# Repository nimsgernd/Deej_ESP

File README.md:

# Deej Fork by Daniel Nimsgern

Original deej project (description below) by omriharel

After this project sat idle for so long due to budget reasons I have decided to revive it. The main changes I am looking at are a custom PCB and a switch to using an ESP32 for ease of use and adding wireless capabilities.

The desired feature list is:
- 6 Slide potentiometers
- 6 Mute buttons (Cherry MX Green Switches)
- 2 Rotary potentiometers with switches
- 8 LED mute indicators
- 12 Slide poentiometer indicators
- 4 SPI 128x64 OLED displays

Ideas for a Rev2:
- Li-Ion battery powered (maybe 18650 or pouch cell)

# deej

deej is an **open-source hardware volume mixer** for Windows and Linux PCs. It lets you use real-life sliders (like a DJ!) to **seamlessly control the volumes of different apps** (such as your music player, the game you're playing and your voice chat session) without having to stop what you're doing.

**Join the [deej Discord server](https://discord.gg/nf88NJu) if you need help or have any questions!**

> **_New:_** [work-in-progress deej FAQ](./docs/faq/faq.md)!

deej consists of a [lightweight desktop client](#features) written in Go, and an Arduino-based hardware setup that's simple and cheap to build. [**Check out some versions built by members of our community!**](./community.md)

**[Download the latest release](https://github.com/omriharel/deej/releases/latest) | [Video demonstration](https://youtu.be/VoByJ4USMr8) | [Build video by Tech Always](https://youtu.be/x2yXbFiiAeI)**

> _**Psst!** [No 3D printer? No problem!](./assets/build-shoebox.jpg)_ You can build deej on some cardboard, a shoebox or even a breadboard :)

## Table of contents

- [Deej Fork by Daniel Nimsgern](#deej-fork-by-daniel-nimsgern)
- [deej](#deej)
  - [Table of contents](#table-of-contents)
  - [Features](#features)
  - [How it works](#how-it-works)
    - [Hardware](#hardware)
      - [Schematic](#schematic)
    - [Software](#software)
  - [Slider mapping (configuration)](#slider-mapping-configuration)
  - [Build your own!](#build-your-own)
    - [FAQ](#faq)
    - [Build video](#build-video)
    - [Bill of Materials](#bill-of-materials)
    - [Thingiverse collection](#thingiverse-collection)
    - [Build procedure](#build-procedure)
  - [How to run](#how-to-run)
    - [Requirements](#requirements)
      - [Windows](#windows)
      - [Linux](#linux)
    - [Download and installation](#download-and-installation)
    - [Building from source](#building-from-source)
  - [Community](#community)
    - [Donations](#donations)
    - [Contributing](#contributing)
  - [License](#license)

## Features

deej is written in Go and [distributed](https://github.com/omriharel/deej/releases/latest) as a portable (no installer needed) executable.

- Bind apps to different sliders
  - Bind multiple apps per slider (i.e. one slider for all your games)
  - Bind the master channel
  - Bind "system sounds" (on Windows)
  - Bind specific audio devices by name (on Windows)
  - Bind currently active app (on Windows)
  - Bind all other unassigned apps
- Control your microphone's input level
- Lightweight desktop client, consuming around 10MB of memory
- Runs from your system tray
- Helpful notifications to let you know if something isn't working

> **Looking for the older Python version?** It's no longer maintained, but you can always find it in the [`legacy-python` branch](https://github.com/omriharel/deej/tree/legacy-python).

## How it works

### Hardware

- The sliders are connected to 5 (or as many as you like) analog pins on an Arduino Nano/Uno board. They're powered from the board's 5V output (see schematic)
- The board connects via a USB cable to the PC

#### Schematic

### Software

- The code running on the Arduino board is a [C program](./arduino/deej-5-sliders-vanilla/deej-5-sliders-vanilla.ino) constantly writing current slider values over its serial interface
- The PC runs a lightweight [Go client](./pkg/deej/cmd/main.go) in the background. This client reads the serial stream and adjusts app volumes according to the given configuration file

## Slider mapping (configuration)

deej uses a simple YAML-formatted configuration file named [`config.yaml`](./config.yaml), placed alongside the deej executable.

The config file determines which applications (and devices) are mapped to which sliders, and which parameters to use for the connection to the Arduino board, as well as other user preferences.

**This file auto-reloads when its contents are changed, so you can change application mappings on-the-fly without restarting deej.**

It looks like this:

```yaml
slider_mapping:
  0: master
  1: chrome.exe
  2: spotify.exe
  3:
    - pathofexile_x64.exe
    - rocketleague.exe
  4: discord.exe

# set this to true if you want the controls inverted (i.e. top is 0%, bottom is 100%)
invert_sliders: false

# settings for connecting to the arduino board
com_port: COM4
baud_rate: 9600

# adjust the amount of signal noise reduction depending on your hardware quality
# supported values are "low" (excellent hardware), "default" (regular hardware) or "high" (bad, noisy hardware)
noise_reduction: default
```

- `master` is a special option to control the master volume of the system _(uses the default playback device)_
- `mic` is a special option to control your microphone's input level _(uses the default recording device)_
- `deej.unmapped` is a special option to control all apps that aren't bound to any slider ("everything else")
- On Windows, `deej.current` is a special option to control whichever app is currently in focus
- On Windows, you can specify a device's full name, i.e. `Speakers (Realtek High Definition Audio)`, to bind that device's level to a slider. This doesn't conflict with the default `master` and `mic` options, and works for both input and output devices.
  - Be sure to use the full device name, as seen in the menu that comes up when left-clicking the speaker icon in the tray menu
- `system` is a special option on Windows to control the "System sounds" volume in the Windows mixer
- All names are case-**in**sensitive, meaning both `chrome.exe` and `CHROME.exe` will work
- You can create groups of process names (using a list) to either:
    - control more than one app with a single slider
    - choose whichever process in the group that's currently running (i.e. to have one slider control any game you're playing)

## Build your own!

Building deej is very simple. You only need a few relatively cheap parts - it's an excellent starter project (and my first Arduino project, personally). Remember that if you need any help or have a question that's not answered here, you can always [join the deej Discord server](https://discord.gg/nf88NJu).

Build deej for yourself, or as an awesome gift for your gaming buddies!

### FAQ

I've started a highly focused effort of writing a proper FAQ page for deej, covering many basic and advanced topics.

It is still _very much a work-in-progress_, but I'm happy to [share it in its current state](./docs/faq/faq.md) in hopes that it at least covers some questions you might have.

FAQ feedback in our [community Discord](https://discord.gg/nf88NJu) is strongly encouraged :)

### Build video

In case you prefer watching to reading, Charles from the [**Tech Always**](https://www.youtube.com/c/TechAlways) YouTube channel has made [**a fantastic video**](https://youtu.be/x2yXbFiiAeI) that covers the basics of building deej for yourself, including parts, costs, assembly and software. I highly recommend checking it out!

### Bill of Materials

- An Arduino Nano, Pro Micro or Uno board
  - I officially recommend using a Nano or a Pro Micro for their smaller form-factor, friendlier USB connectors and more analog pins. Plus they're cheaper
  - You can also use any other development board that has a Serial over USB interface
- A few slider potentiometers, up to your number of free analog pins (the cheaper ones cost around 1-2 USD each, and come with a standard 10K Ohm variable resistor. These _should_ work just fine for this project)
  - **Important:** make sure to get **linear** sliders, not logarithmic ones! Check the product description
  - You can also use circular knobs if you like
- Some wires
- Any kind of box to hold everything together. **You don't need a 3D printer for this project!** It works fantastically with just a piece of cardboard or a shoebox. That being said, if you do have one, read on...

### Thingiverse collection

With many different 3D-printed designs being added to our [community showcase](./community.md), it felt right to gather all of them in a Thingiverse collection for you to browse. If you have access to a 3D printer, feel free to use one of the designs in your build.

**[Visit our community-created design collection on Thingiverse!](https://thingiverse.com/omriharel/collections/deej)**

> You can also [submit your own](https://discord.gg/nf88NJu) design to be added to the collection. Regardless, if you do upload your design to Thingiverse, _please add a `deej` tag to it so that others can find it more easily_.

### Build procedure

- Connect everything according to the [schematic](#schematic)
- Test with a multimeter to be sure your sliders are hooked up correctly
- Flash the Arduino chip with the sketch in [`arduino\deej-5-sliders-vanilla`](./arduino/deej-5-sliders-vanilla/deej-5-sliders-vanilla.ino)
  - _Important:_ If you have more or less than 5 sliders, you must edit the sketch to match what you have
- After flashing, check the serial monitor. You should see a constant stream of values separated by a pipe (`|`) character, e.g. `0|240|1023|0|483`
  - When you move a slider, its corresponding value should move between 0 and 1023
- Congratulations, you're now ready to run the deej executable!

## How to run

### Requirements

#### Windows

- Windows. That's it

#### Linux

- Install `libgtk-3-dev`, `libappindicator3-dev` and `libwebkit2gtk-4.0-dev` for system tray support. Pre-built Linux binaries aren't currently released, so you'll need to [build from source](#building-from-source). If there's demand for pre-built binaries, please [let me know](https://discord.gg/nf88NJu)!

### Download and installation

- Head over to the [releases page](https://github.com/omriharel/deej/releases) and download the [latest version](https://github.com/omriharel/deej/releases/latest)'s executable and configuration file (`deej.exe` and `config.yaml`)
- Place them in the same directory anywhere on your machine
- (Optional, on Windows) Create a shortcut to `deej.exe` and copy it to `%APPDATA%\Microsoft\Windows\Start Menu\Programs\Startup` to have deej run on boot

### Building from source

If you'd rather not download a compiled executable, or want to extend deej or modify it to your needs, feel free to clone the repository and build it yourself. All you need is a Go 1.14 (or above) environment on your machine. If you go this route, make sure to check out the [developer scripts](./pkg/deej/scripts).

Like other Go packages, you can also use the `go get` tool: `go get -u github.com/omriharel/deej`. Please note that the package code now resides in the `pkg/deej` directory, and needs to be imported from there if used inside another project.

If you need any help with this, please [join our Discord server](https://discord.gg/nf88NJu).

## Community

deej is a relatively new project, but a vibrant and awesome community is rapidly growing around it. Come hang out with us in the [deej Discord server](https://discord.gg/nf88NJu), or check out a whole bunch of cool and creative builds made by our members in the [community showcase](./community.md).

The server is also a great place to ask questions, suggest features or report bugs (but of course, feel free to use GitHub if you prefer).

### Donations

If you love deej and want to show your support for this project, you can do so using the link below. Please don't feel obligated to donate - building the project and telling your friends about it goes a very long way! Thank you very much.

### Contributing

Please see [`docs/CONTRIBUTING.md`](./docs/CONTRIBUTING.md).

## License

deej is released under the [MIT license](./LICENSE).

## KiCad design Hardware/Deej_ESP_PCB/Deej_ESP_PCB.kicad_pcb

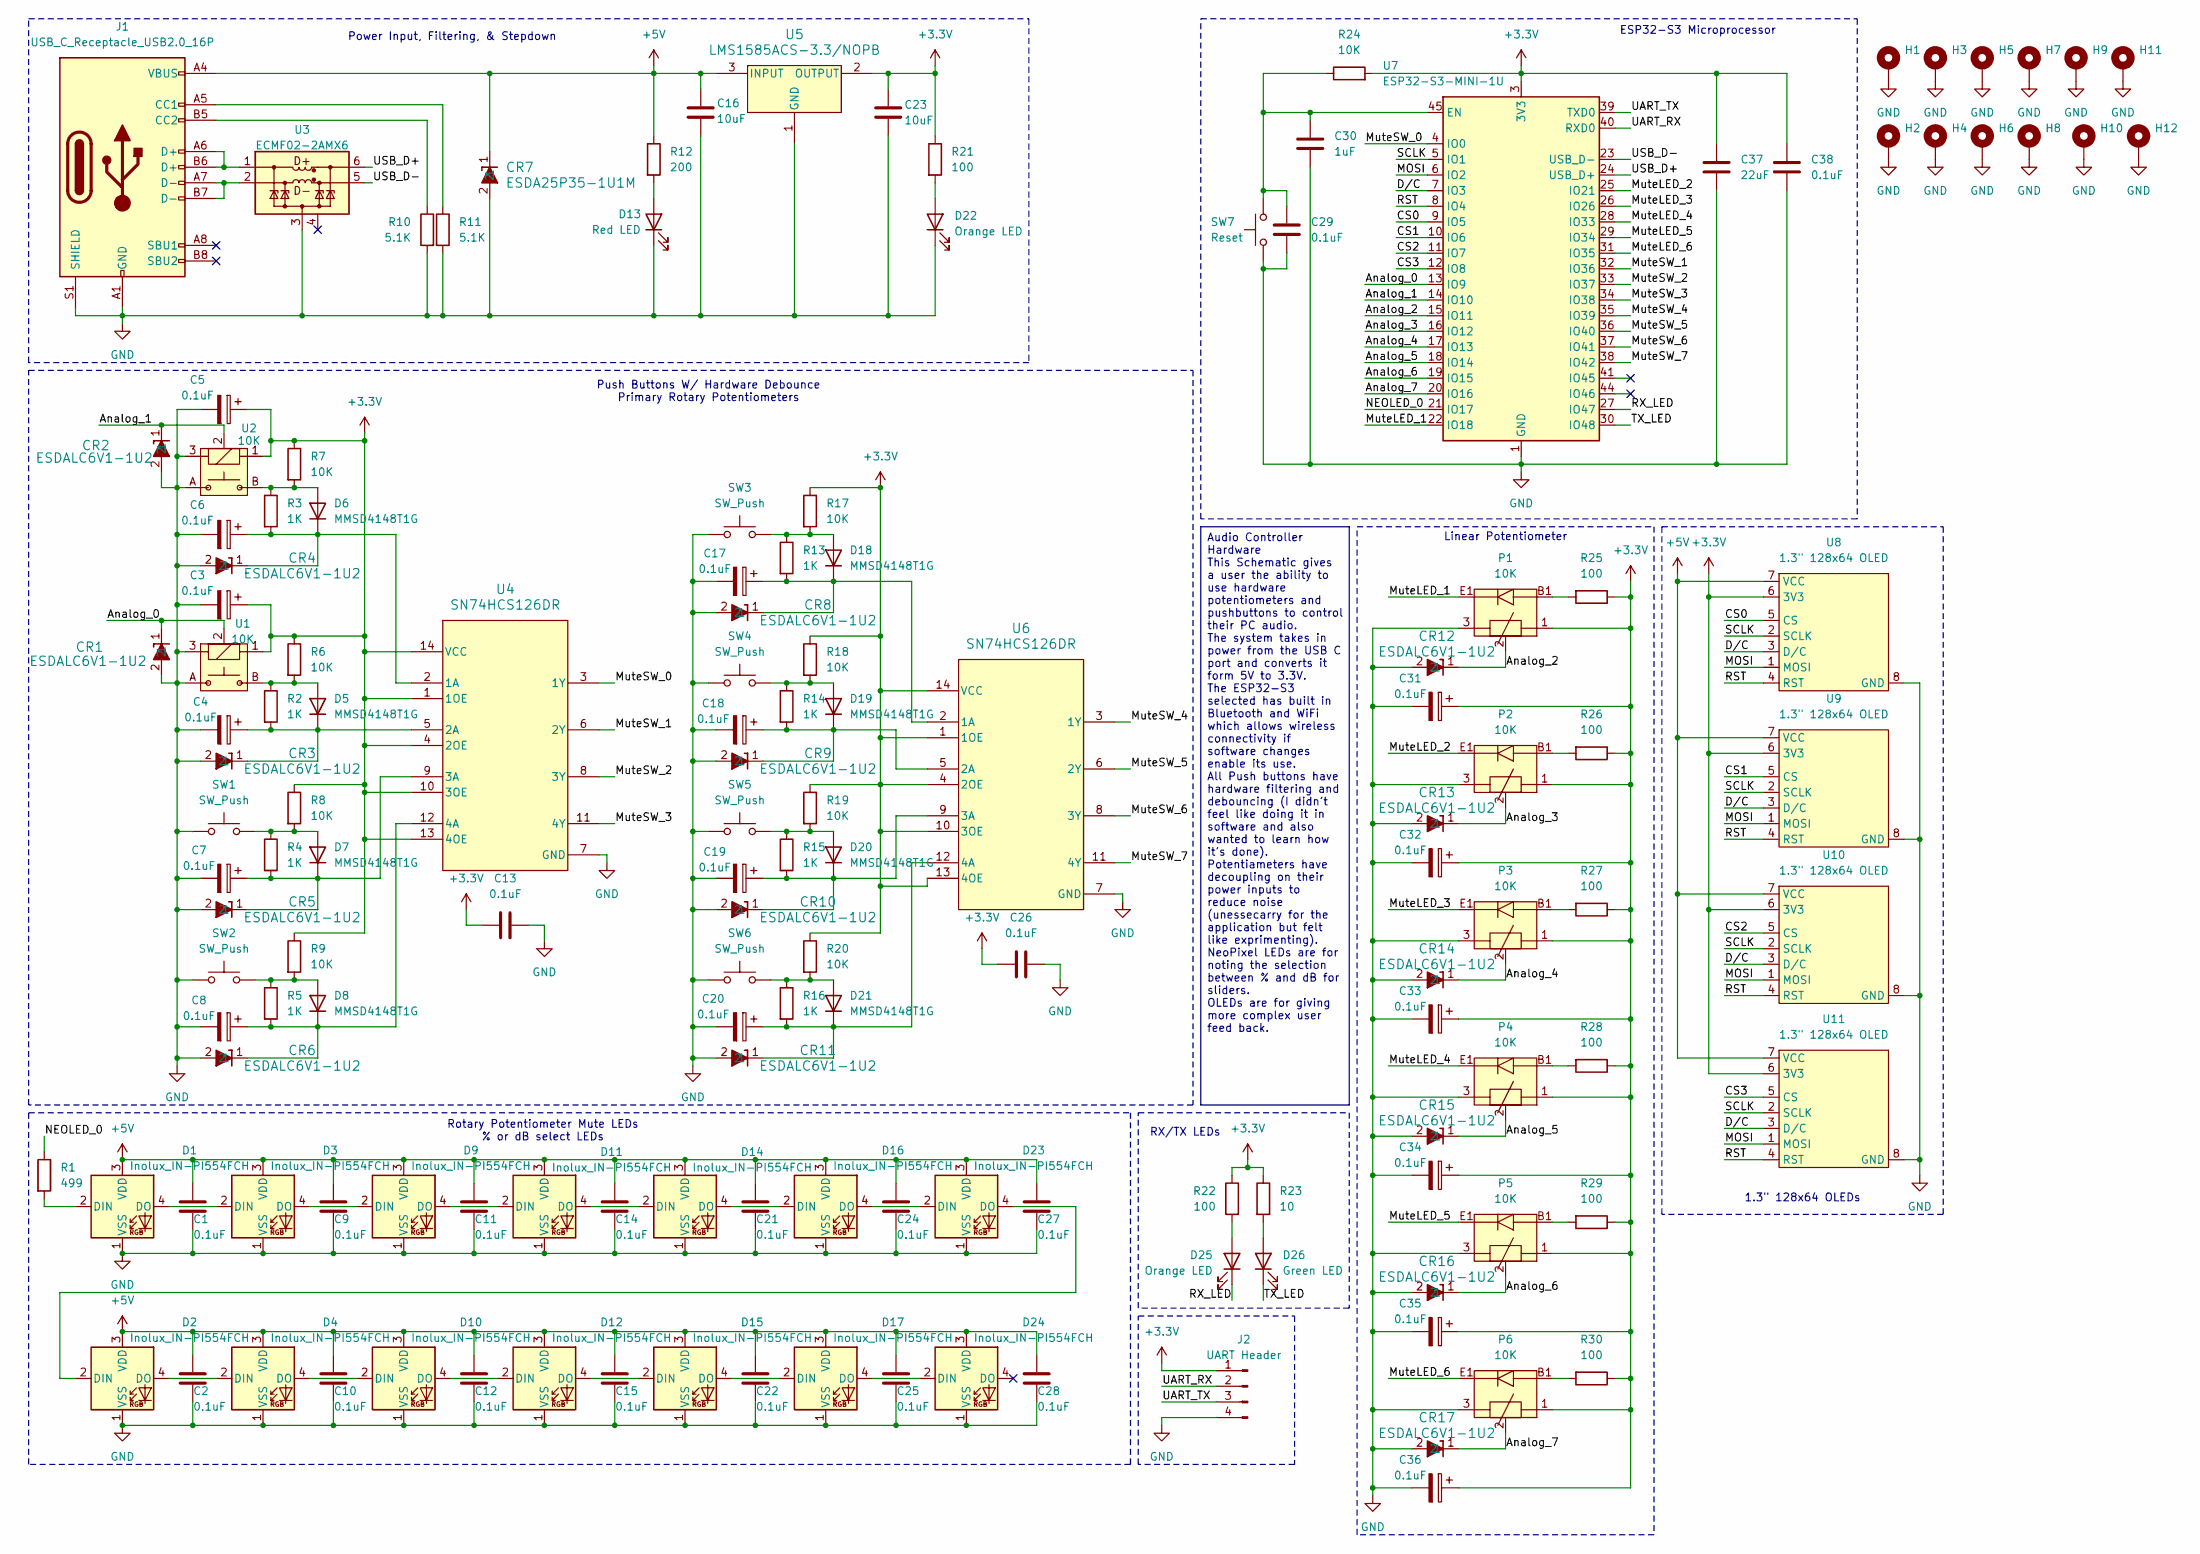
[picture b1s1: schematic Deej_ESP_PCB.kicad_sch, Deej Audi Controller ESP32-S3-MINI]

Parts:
C1, C2, C9, C10, C11, C12, C13, C14, C15, C21, C22, C24, C25, C26, C27, C28, C29, C38: 0.1uF; C_0603_1608Metric_Pad1.08x0.95mm_HandSolder
C3, C4, C5, C6, C7, C8, C17, C18, C19, C20, C31, C32, C33, C34, C35, C36: 0.1uF; CP_EIA-3216-18_Kemet-A_HandSolder
C16, C23: 10uF; C_0603_1608Metric_Pad1.08x0.95mm_HandSolder
C30: 1uF; C_0603_1608Metric_Pad1.08x0.95mm_HandSolder
C37: 22uF; C_0603_1608Metric_Pad1.08x0.95mm_HandSolder
CR1, CR2, CR3, CR4, CR5, CR6, CR8, CR9, CR10, CR11, CR12, CR13, CR14, CR15, CR16, CR17: ESDALC6V1-1U2; DIODE_ESDALC6V1-1U2_STM
CR7: ESDA25P35-1U1M; QFN1610_STM
D1, D2, D3, D4, D9, D10, D11, D12, D14, D15, D16, D17, D23, D24: Inolux_IN-PI554FCH; LED_Inolux_IN-PI554FCH_PLCC4_5.0x5.0mm_P3.2mm
D5, D6, D7, D8, D18, D19, D20, D21: MMSD4148T1G; D_SOD-123
D13: Red LED; LED_0603_1608Metric_Pad1.05x0.95mm_HandSolder
D22, D25: Orange LED; LED_0603_1608Metric_Pad1.05x0.95mm_HandSolder
D26: Green LED; LED_0603_1608Metric_Pad1.05x0.95mm_HandSolder
H1, H3, H5, H7, H9: MountingHole_3.2mm_M3_Pad
H2, H4, H6, H8, H10, H11, H12: MountingHole_Pad; MountingHole_3.2mm_M3_Pad
J1: USB_C_Receptacle_USB2.0_16P; USB_C_Receptacle_GCT_USB4085
J2: UART Header; PinHeader_1x04_P2.54mm_Vertical
P1, P2, P3, P4, P5, P6: 10K; PTL0115R0103B1
R1: 499; C_0603_1608Metric_Pad1.08x0.95mm_HandSolder
R2, R3, R4, R5, R13, R14, R15, R16: 1K; C_0603_1608Metric_Pad1.08x0.95mm_HandSolder
R6, R7, R8, R9, R17, R18, R19, R20, R24: 10K; C_0603_1608Metric_Pad1.08x0.95mm_HandSolder
R10, R11: 5.1K; C_0603_1608Metric_Pad1.08x0.95mm_HandSolder
R12: 200; C_0603_1608Metric_Pad1.08x0.95mm_HandSolder
R21, R22, R25, R26, R27, R28, R29, R30: 100; C_0603_1608Metric_Pad1.08x0.95mm_HandSolder
R23: 10; C_0603_1608Metric_Pad1.08x0.95mm_HandSolder
SW1, SW2, SW3, SW4, SW5, SW6: SW_Push; SW_Cherry_MX_PCB
SW7: Reset; SWITCH_FSMSM_TYC
U1, U2: 10K; 39LA-1PB-103
U3: ECMF02-2AMX6; QFN-6L_STM
U4, U6: SN74HCS126DR; D0014A-IPC_A
U5: LMS1585ACS-3.3/NOPB; KTT0003B
U7: ESP32-S3-MINI-1U; ESP32S3MINI1UN8
U8, U9, U10, U11: 1.3" 128x64 OLED; Adafruit_1_3_OLED

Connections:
+3.3V: C3.1, C5.1, C13.2, C23.1, C26.2, C31.1, C32.1, C33.1, C34.1, C35.1, C36.1, C37.1, C38.1, J2.1, P1.1, P2.1, P3.1, P4.1, P5.1, P6.1, R6.1, R7.1, R8.1, R9.1, R17.1, R18.1, R19.1, R20.1, R21.1, R22.1, R23.1, R24.2, R25.1, R26.1, R27.1, R28.1, R29.1, R30.1, U1.1, U2.1, U4.1 (1OE), U4.4 (2OE), U4.10 (3OE), U4.13 (4OE), U4.14 (VCC), U5.2 (OUTPUT), U5.4 (OUTPUT), U6.1 (1OE), U6.4 (2OE), U6.10 (3OE), U6.13 (4OE), U6.14 (VCC), U7.3 (3V3), U8.6 (3V3), U9.6 (3V3), U10.6 (3V3), U11.6 (3V3)
+5V: C1.1, C2.1, C9.1, C10.1, C11.1, C12.1, C14.1, C15.1, C16.1, C21.1, C22.1, C24.1, C25.1, C27.1, C28.1, CR7.1, D1.3 (VDD), D2.3 (VDD), D3.3 (VDD), D4.3 (VDD), D9.3 (VDD), D10.3 (VDD), D11.3 (VDD), D12.3 (VDD), D14.3 (VDD), D15.3 (VDD), D16.3 (VDD), D17.3 (VDD), D23.3 (VDD), D24.3 (VDD), J1.A4 (VBUS), J1.A9 (VBUS), J1.B4 (VBUS), J1.B9 (VBUS), R12.1, U5.3 (INPUT), U8.7 (VCC), U9.7 (VCC), U10.7 (VCC), U11.7 (VCC)
/Analog_0: CR1.1, U1.2, U7.13 (IO9)
/Analog_1: CR2.1, U2.2, U7.14 (IO10)
/Analog_2: CR12.1, P1.2, U7.15 (IO11)
/Analog_3: CR13.1, P2.2, U7.16 (IO12)
/Analog_4: CR14.1, P3.2, U7.17 (IO13)
/Analog_5: CR15.1, P4.2, U7.18 (IO14)
/Analog_6: CR16.1, P5.2, U7.19 (IO15)
/Analog_7: CR17.1, P6.2, U7.20 (IO16)
/CS0: U7.9 (IO5), U8.5 (CS)
/CS1: U7.10 (IO6), U9.5 (CS)
/CS2: U7.11 (IO7), U10.5 (CS)
/CS3: U7.12 (IO8), U11.5 (CS)
/D/C: U7.7 (IO3), U8.3 (D/C), U9.3 (D/C), U10.3 (D/C), U11.3 (D/C)
/MOSI: U7.6 (IO2), U8.1 (MOSI), U9.1 (MOSI), U10.1 (MOSI), U11.1 (MOSI)
/MuteLED_1: P1.E1, U7.22 (IO18)
/MuteLED_2: P2.E1, U7.25 (IO21)
/MuteLED_3: P3.E1, U7.26 (IO26)
/MuteLED_4: P4.E1, U7.28 (IO33)
/MuteLED_5: P5.E1, U7.29 (IO34)
/MuteLED_6: P6.E1, U7.31 (IO35)
/MuteSW_0: U4.3 (1Y), U7.4 (IO0)
/MuteSW_1: U4.6 (2Y), U7.32 (IO36)
/MuteSW_2: U4.8 (3Y), U7.33 (IO37)
/MuteSW_3: U4.11 (4Y), U7.34 (IO38)
/MuteSW_4: U6.3 (1Y), U7.35 (IO39)
/MuteSW_5: U6.6 (2Y), U7.36 (IO40)
/MuteSW_6: U6.8 (3Y), U7.37 (IO41)
/MuteSW_7: U6.11 (4Y), U7.38 (IO42)
/NEOLED_0: R1.1, U7.21 (IO17)
/RST: U7.8 (IO4), U8.4 (RST), U9.4 (RST), U10.4 (RST), U11.4 (RST)
/RX_LED: D25.1 (K), U7.27 (IO47)
/SCLK: U7.5 (IO1), U8.2 (SCLK), U9.2 (SCLK), U10.2 (SCLK), U11.2 (SCLK)
/TX_LED: D26.1 (K), U7.30 (IO48)
/UART_RX: J2.2, U7.40 (RXD0)
/UART_TX: J2.3, U7.39 (TXD0)
/USB_D+: U3.6 (D+_out), U7.24 (USB_D+)
/USB_D-: U3.5 (D-_out), U7.23 (USB_D-)
GND: C1.2, C2.2, C3.2, C4.2, C5.2, C6.2, C7.2, C8.2, C9.2, C10.2, C11.2, C12.2, C13.1, C14.2, C15.2, C16.2, C17.2, C18.2, C19.2, C20.2, C21.2, C22.2, C23.2, C24.2, C25.2, C26.1, C27.2, C28.2, C29.2, C30.2, C31.2, C32.2, C33.2, C34.2, C35.2, C36.2, C37.2, C38.2, CR1.2, CR2.2, CR3.2, CR4.2, CR5.2, CR6.2, CR7.2, CR8.2, CR9.2, CR10.2, CR11.2, CR12.2, CR13.2, CR14.2, CR15.2, CR16.2, CR17.2, D1.1 (VSS), D2.1 (VSS), D3.1 (VSS), D4.1 (VSS), D9.1 (VSS), D10.1 (VSS), D11.1 (VSS), D12.1 (VSS), D13.1 (K), D14.1 (VSS), D15.1 (VSS), D16.1 (VSS), D17.1 (VSS), D22.1 (K), D23.1 (VSS), D24.1 (VSS), H1.1, H2.1, H3.1, H4.1, H5.1, H6.1, H7.1, H8.1, H9.1, H10.1, H11.1, H12.1, J1.A1 (GND), J1.A12 (GND), J1.B1 (GND), J1.B12 (GND), J1.S1 (SHIELD), J2.4, P1.3, P2.3, P3.3, P4.3, P5.3, P6.3, R10.2, R11.2, SW1.1, SW2.1, SW3.1, SW4.1, SW5.1, SW6.1, SW7.1, U1.3, U1.A, U2.3, U2.A, U3.3 (GND), U4.7 (GND), U5.1 (GND), U6.7 (GND), U7.1 (GND), U7.2 (GND), U7.42 (GND), U7.43 (GND), U7.46 (GND), U7.47 (GND), U7.48 (GND), U7.49 (GND), U7.50 (GND), U7.51 (GND), U7.52 (GND), U7.53 (GND), U7.54 (GND), U7.55 (GND), U7.56 (GND), U7.57 (GND), U7.58 (GND), U7.59 (GND), U7.60 (GND), U7.61 (GND), U7.62 (GND), U7.63 (GND), U7.64 (GND), U7.65 (GND), U7.66 (GND), U7.67 (GND), U7.68 (GND), U7.69 (GND), U7.70 (GND), U7.71 (GND), U7.72 (GND), U7.73 (GND), U8.8 (GND), U9.8 (GND), U10.8 (GND), U11.8 (GND)
unnamed: D1.2 (DIN), R1.2
unnamed: D1.4 (DO), D3.2 (DIN)
unnamed: D2.2 (DIN), D23.4 (DO)
unnamed: D2.4 (DO), D4.2 (DIN)
unnamed: D3.4 (DO), D9.2 (DIN)
unnamed: D5.2 (A), R2.1, R6.2, U1.B
unnamed: C4.1, CR3.1, D5.1 (K), R2.2, U4.5 (2A)
unnamed: D6.2 (A), R3.1, R7.2, U2.B
unnamed: C6.1, CR4.1, D6.1 (K), R3.2, U4.2 (1A)
unnamed: D7.2 (A), R4.1, R8.2, SW1.2
unnamed: C7.1, CR5.1, D7.1 (K), R4.2, U4.9 (3A)
unnamed: D8.2 (A), R5.1, R9.2, SW2.2
unnamed: C8.1, CR6.1, D8.1 (K), R5.2, U4.12 (4A)
unnamed: D4.4 (DO), D10.2 (DIN)
unnamed: D10.4 (DO), D12.2 (DIN)
unnamed: D9.4 (DO), D11.2 (DIN)
unnamed: D11.4 (DO), D14.2 (DIN)
unnamed: D12.4 (DO), D15.2 (DIN)
unnamed: D13.2 (A), R12.2
unnamed: D14.4 (DO), D16.2 (DIN)
unnamed: D15.4 (DO), D17.2 (DIN)
unnamed: D16.4 (DO), D23.2 (DIN)
unnamed: D17.4 (DO), D24.2 (DIN)
unnamed: D18.2 (A), R13.1, R17.2, SW3.2
unnamed: C17.1, CR8.1, D18.1 (K), R13.2, U6.2 (1A)
unnamed: D19.2 (A), R14.1, R18.2, SW4.2
unnamed: C18.1, CR9.1, D19.1 (K), R14.2, U6.5 (2A)
unnamed: D20.2 (A), R15.1, R19.2, SW5.2
unnamed: C19.1, CR10.1, D20.1 (K), R15.2, U6.9 (3A)
unnamed: D21.2 (A), R16.1, R20.2, SW6.2
unnamed: C20.1, CR11.1, D21.1 (K), R16.2, U6.12 (4A)
unnamed: D22.2 (A), R21.2
unnamed: D25.2 (A), R22.2
unnamed: D26.2 (A), R23.2
unnamed: J1.A5 (CC1), R11.1
unnamed: J1.B5 (CC2), R10.1
unnamed: P1.B1, R25.2
unnamed: P2.B1, R26.2
unnamed: P3.B1, R27.2
unnamed: P4.B1, R28.2
unnamed: P5.B1, R29.2
unnamed: P6.B1, R30.2
unnamed: J1.A6 (D+), J1.B6 (D+), U3.1 (D+_in)
unnamed: J1.A7 (D-), J1.B7 (D-), U3.2 (D-_in)
unnamed: C29.1, C30.1, R24.1, SW7.2, U7.45 (EN)

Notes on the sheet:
Push Buttons W/ Hardware Debounce Primary Rotary Potentiometers
Linear Potentiometer
Rotary Potentiometer Mute LEDs % or dB select LEDs
RX/TX LEDs
1.3" 128x64 OLEDs
ESP32-S3 Microprocessor
Power Input, Filtering, & Stepdown
Audio Controller Hardware This Schematic gives a user the ability to use hardware potentiometers and pushbuttons to control their PC audio. The system takes in power from the USB C port and converts it form 5V to 3.3V. The ESP32-S3 selected has built in Bluetooth and WiFi which allows wireless conn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

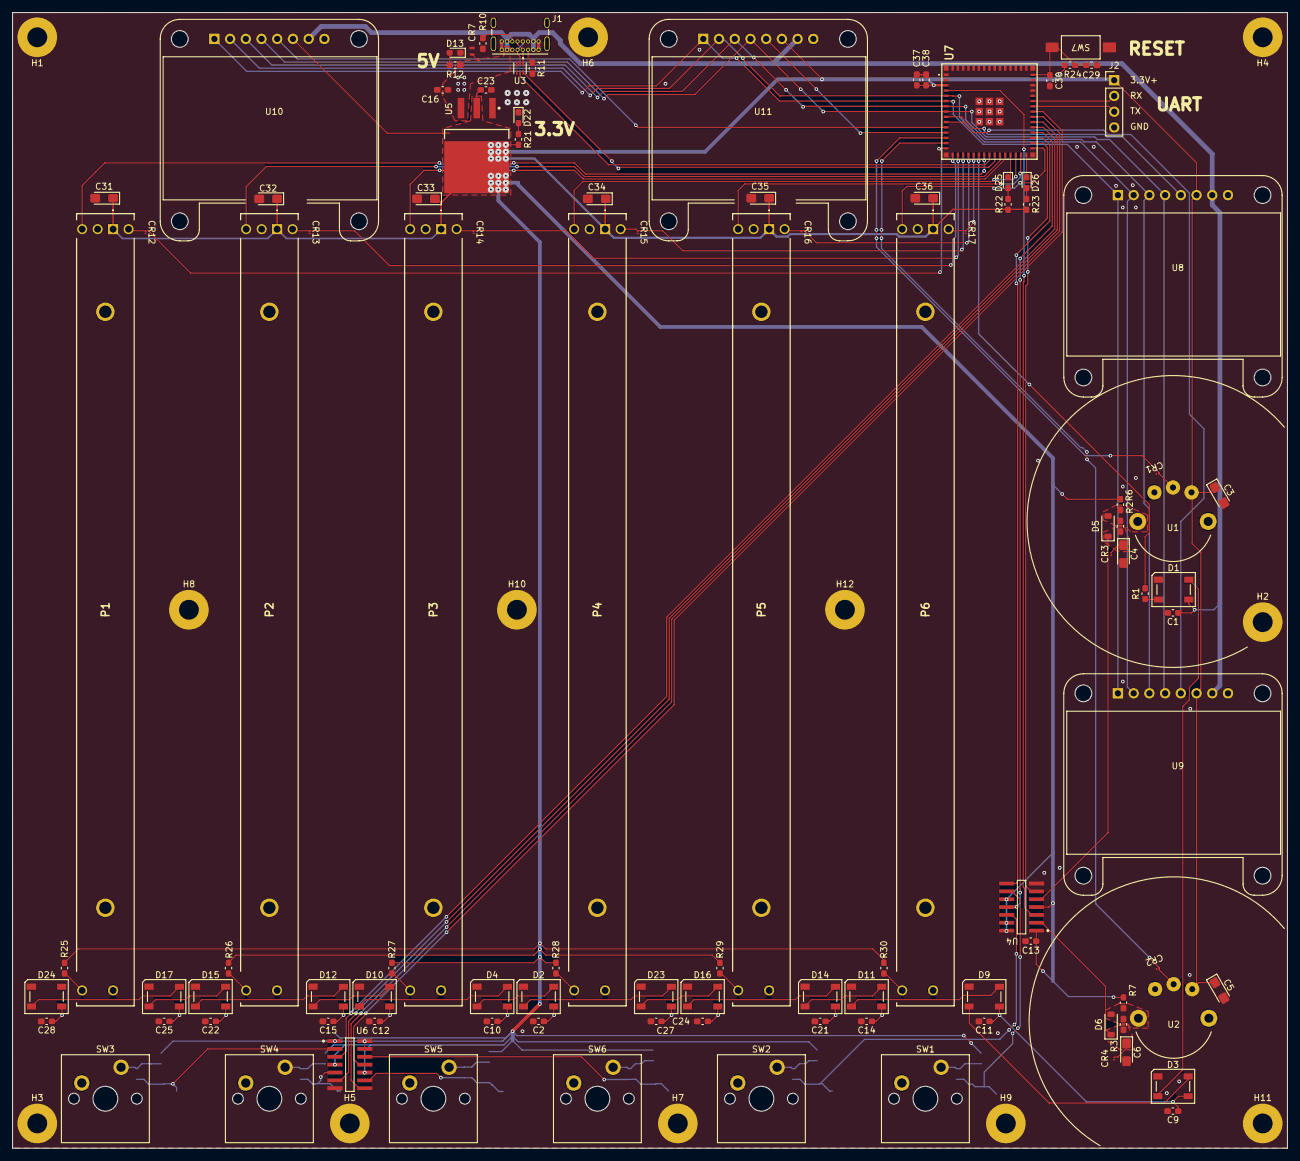
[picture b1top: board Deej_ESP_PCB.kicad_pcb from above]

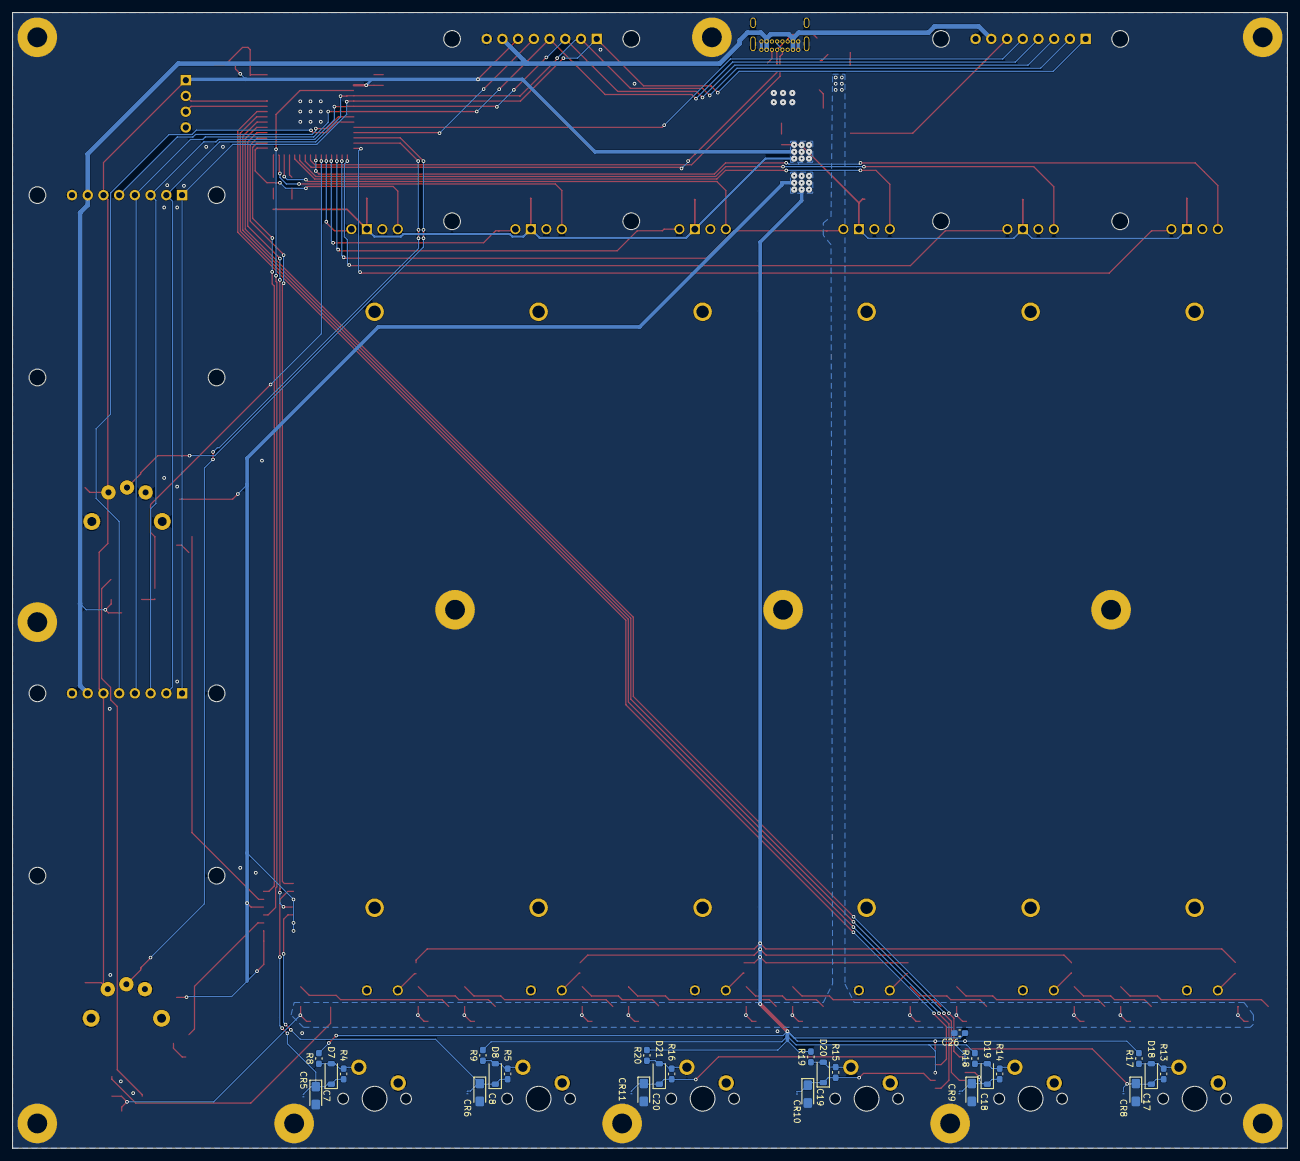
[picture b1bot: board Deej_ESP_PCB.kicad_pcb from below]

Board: 2 copper layers, 206.0 x 183.5 mm, 149 parts (31 on the bottom side), 85 nets.

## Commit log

2025-07-27 New file structure to better suit the changes I have planned.
2025-07-27 New direction for the porject
2025-07-27 Initial KiCAD project set up and decided to go with the ESP32 S3 Mini 1U N8 as the MCU.
2025-08-01 Started brainstorming for major components. So far decided on MCU, LEDs, OLED displays, slide potentiameters, and GPIO expanders. Based on the price I am considering changing some of the quantities..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
2025-08-05 Adding components to the part library
2025-08-05 Chose Cherry MX Green Switches for the mute buttons for that good decisive click
2025-08-07 Figured out componentes for hardware debouncing and making sure all components have 3D models for when it comes time to make an enclosure
2025-08-08 Quick update to the README due to a slight scope change
2025-08-09 3D File, ESD, and Old File Clean up
    * Added the 3D files for the rotary potentiometer with switch.
    * Started adding ESD diodes to components the user will touch regularly.
    * Removed old files that won't be used.
2025-08-10 USB Supporting Hardware, 3D Models, BOM Updates
    * Added supporting hardware for the USB C connector
    * Ensured all current components have 3D models
    * Updated the BOM with components for the USB connector
2025-08-10 README Update
2025-08-11 Added Footprints and 3D Files
    - Added the proper footprint and 3D file for the ESP32
    - Added the footprint and 3D file for the USB choke/ESD so the project
    doesn't rely on an external library
    - Added the power step down circuit and LED indicators
    - Added a user LED for program status
    - Made a "Good Enough for Government Work" symbol and footprint for
2025-08-19 Converted From KiCAD Nightly to Stable
    I realized that I had been using the nightly version instead of the
    stable release which became an issue when my nightly broke and all
    more recent nightly builds have had issues building.
    - The main change was just changing the version and generator version
    in the schematic and PCB files.
    - The schematic file had some pin and power settings that were not
2025-08-19 Delete Hardware/Deej_ESP_PCB/Deej_ESP_PCB.kicad_prl
    This auto generated project view preferences file should not have been pushed. Not quite sure why the .gitignore didn't work.
2025-08-20 Migrated Project Footprints to KiCAD Stable
    - I updated the project footprints to be compatable with KiCAD stable
    release.
    - I replaced the footprint for the slide potentiometer.
    - I corrected the Adafruit display in the BOM sheet since I swapped it
    out a few commits ago.
2025-08-21 Added a disclaimer about my feeling on GitHub
2025-08-21 Still dealing with KiCAD Migration issues
    - Had to spend way too much time fixing the libraries.
    - Adjusted the Adafruit 1.3" OLED footprint 3D model to use a lower
    profile pin headder.
    - Added the lower profile pins to the BOM.
    - Went through some of the ERC and fixed some issues (most relating to
    the library issues mentioned above).
2025-08-23 Finished Schemtic 🎉 For now...
    - Added supporting hardware for the ESP32-S3 (decoupling capacitors and
    reset button)
    - Added hardware support for a UART conntection (hoping I won't need to
    use it but you never know)
    - Fixed all ERC issues
    - Replaced the original 11mm stand offs with 8mm stand offs for the
2025-08-31 Synced the KiCAD BOM and my handmade BOM
2025-09-04 Started PCB Layout Added Mounting Holes and Knobs
    - Started doing PCB layout. I have an idea of large component placement
    and therefore overall board size but still working out finalizing
    them.
    - Added platted mounting holes to the board mostly for support since
    most of this board is user interfaces I expect there to be a good
    amount of force applied to the sliders, buttons, and knobs.
2025-09-16 All Components Placed and OSH Park Rules Set.
    - I have placed all of the components and I am looking at starting trace
    layout.
    - I have also set the rules and board stack up specifications for OSH
    Park to ensure thaat the design is as similr to how the final product
    will be.
2025-11-08 Getting Back into it
    I had gotten a little more busy and wasn't able to get back to it.
    - Routed some more power traces
    - Routed the analog signals for the slide potentiometers
2025-11-19 More Power Routing and NEO Pixel LED Routing
    - Added more +3.3V voltage routing
    - Added some signaling for the NEO Pixel LEDs
    TODO: Other LED traces and analog dials
2025-12-05 Finished Running Traces, On to DRC Fixes
    - I believe I finished running the traces to get everything connected
    KiCAD shows one more air wire but that seems like a visual isses since
    I can confirm it is connected.
    - Next I will be starting on fixing the 94 DRC ERRORs. A lot of them
    seems really simple on first glance so I'm not worried about those but
    there are a few errors involving clearances and manufacturing minimums.
2026-06-07 -Trace routing 'done' ... until I find another issue -Fixing DRC errors and warnings
